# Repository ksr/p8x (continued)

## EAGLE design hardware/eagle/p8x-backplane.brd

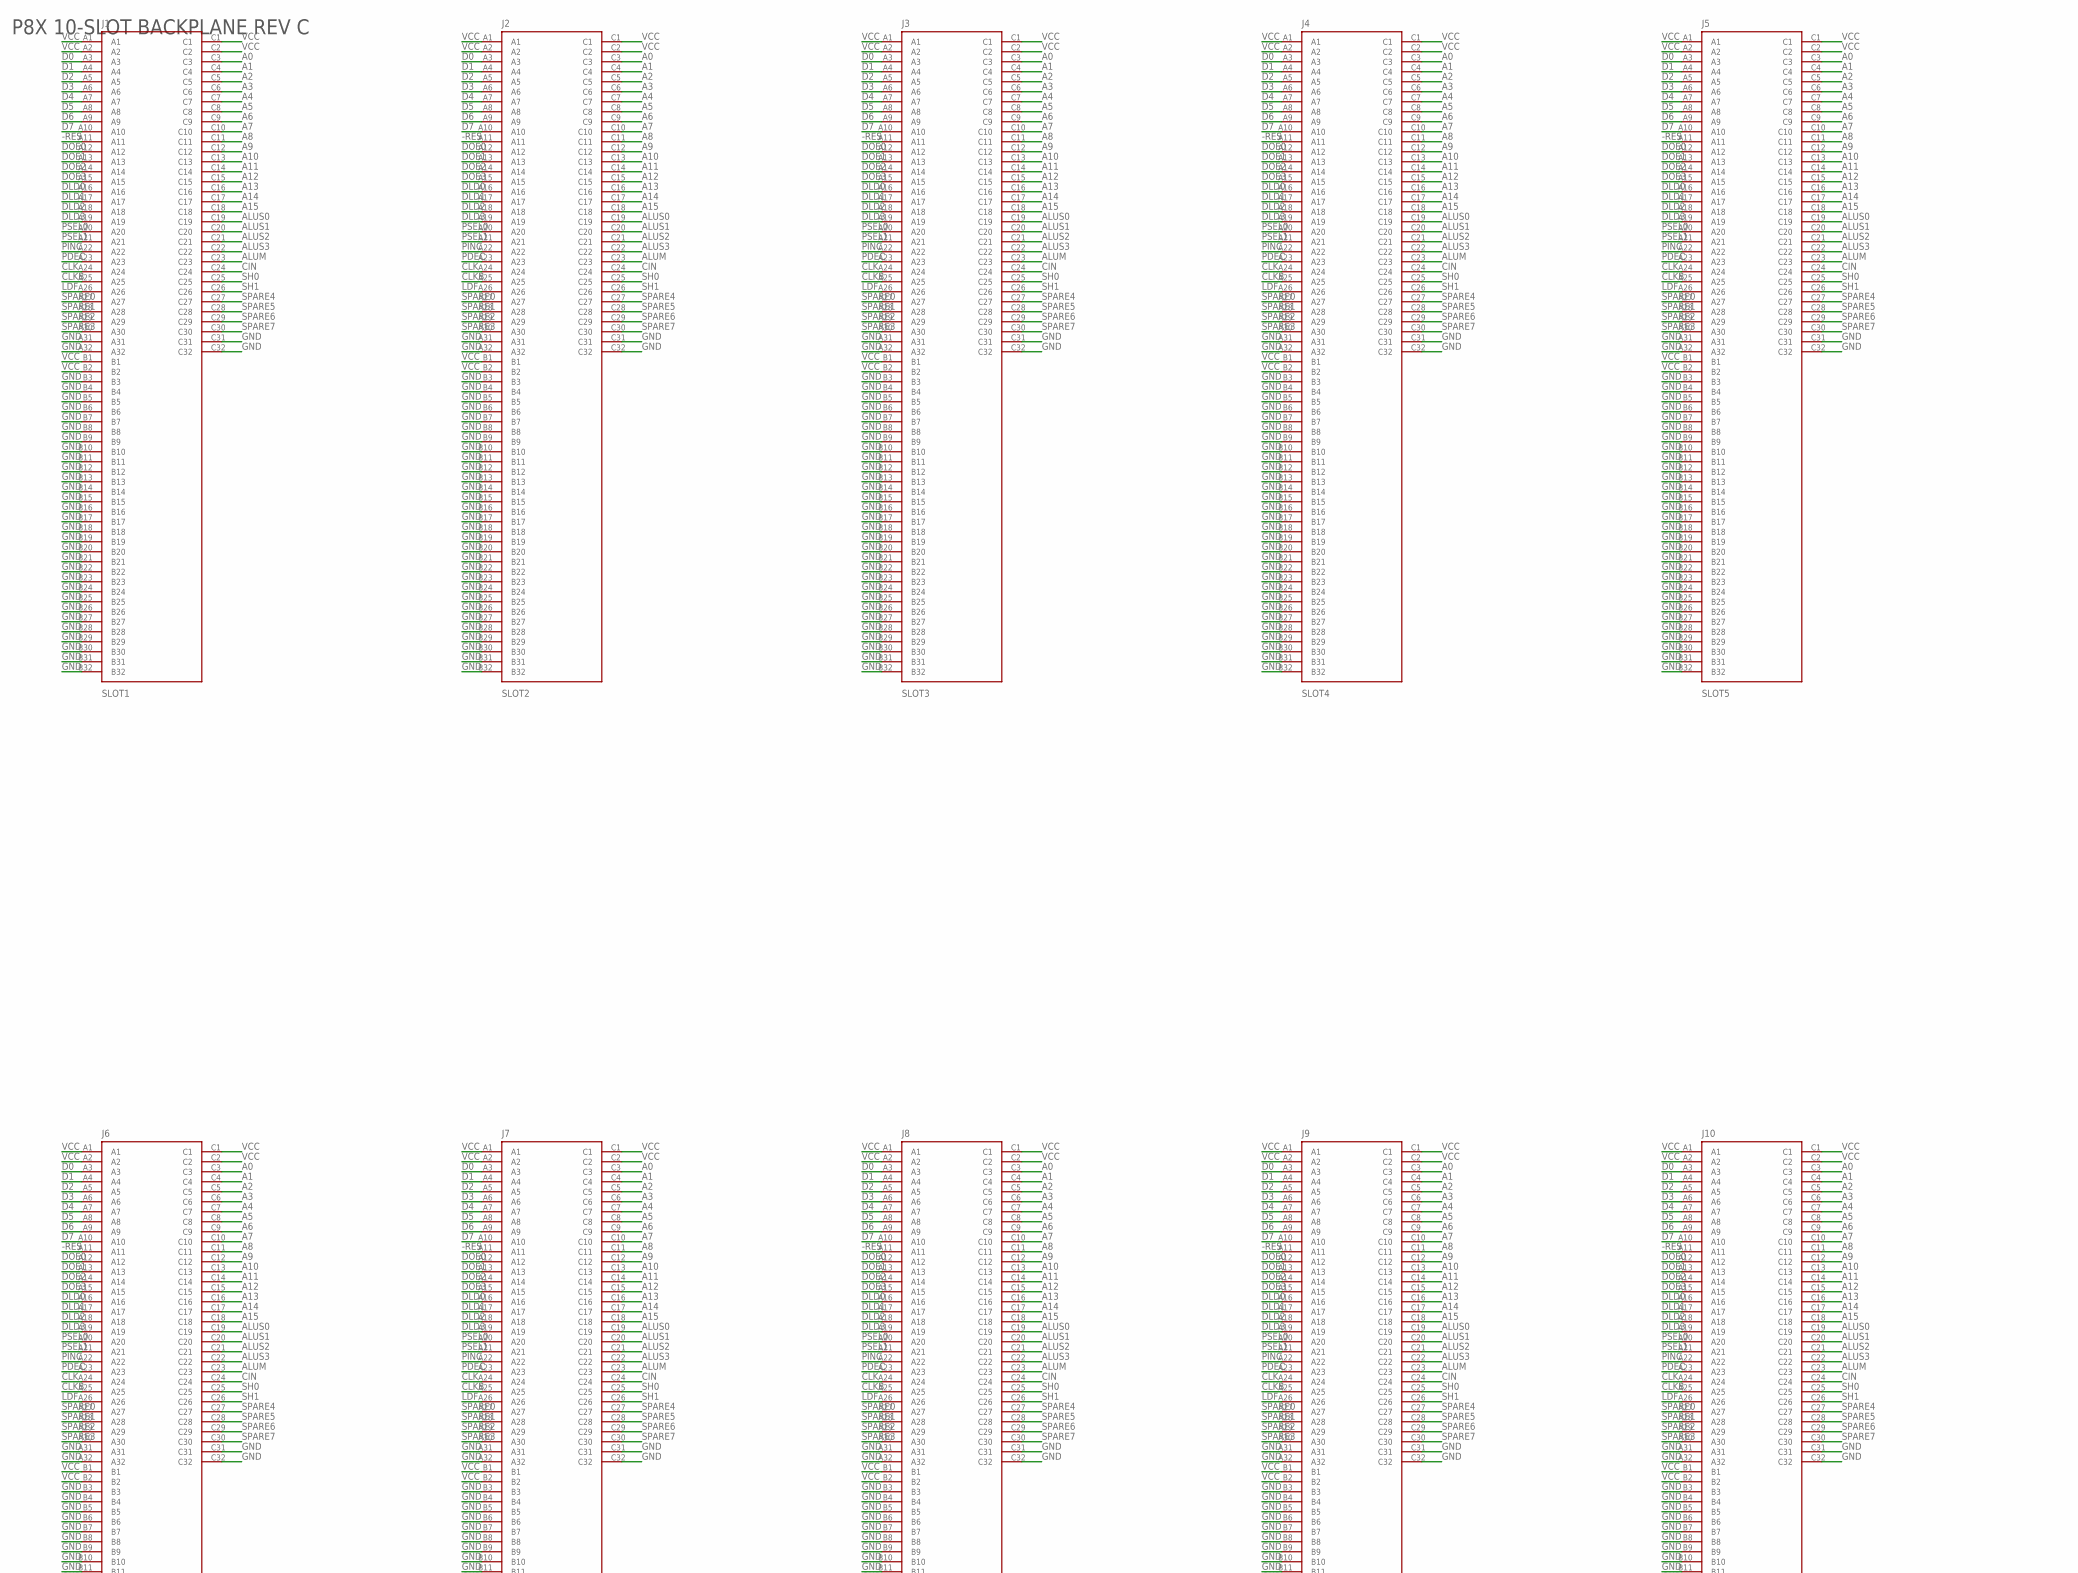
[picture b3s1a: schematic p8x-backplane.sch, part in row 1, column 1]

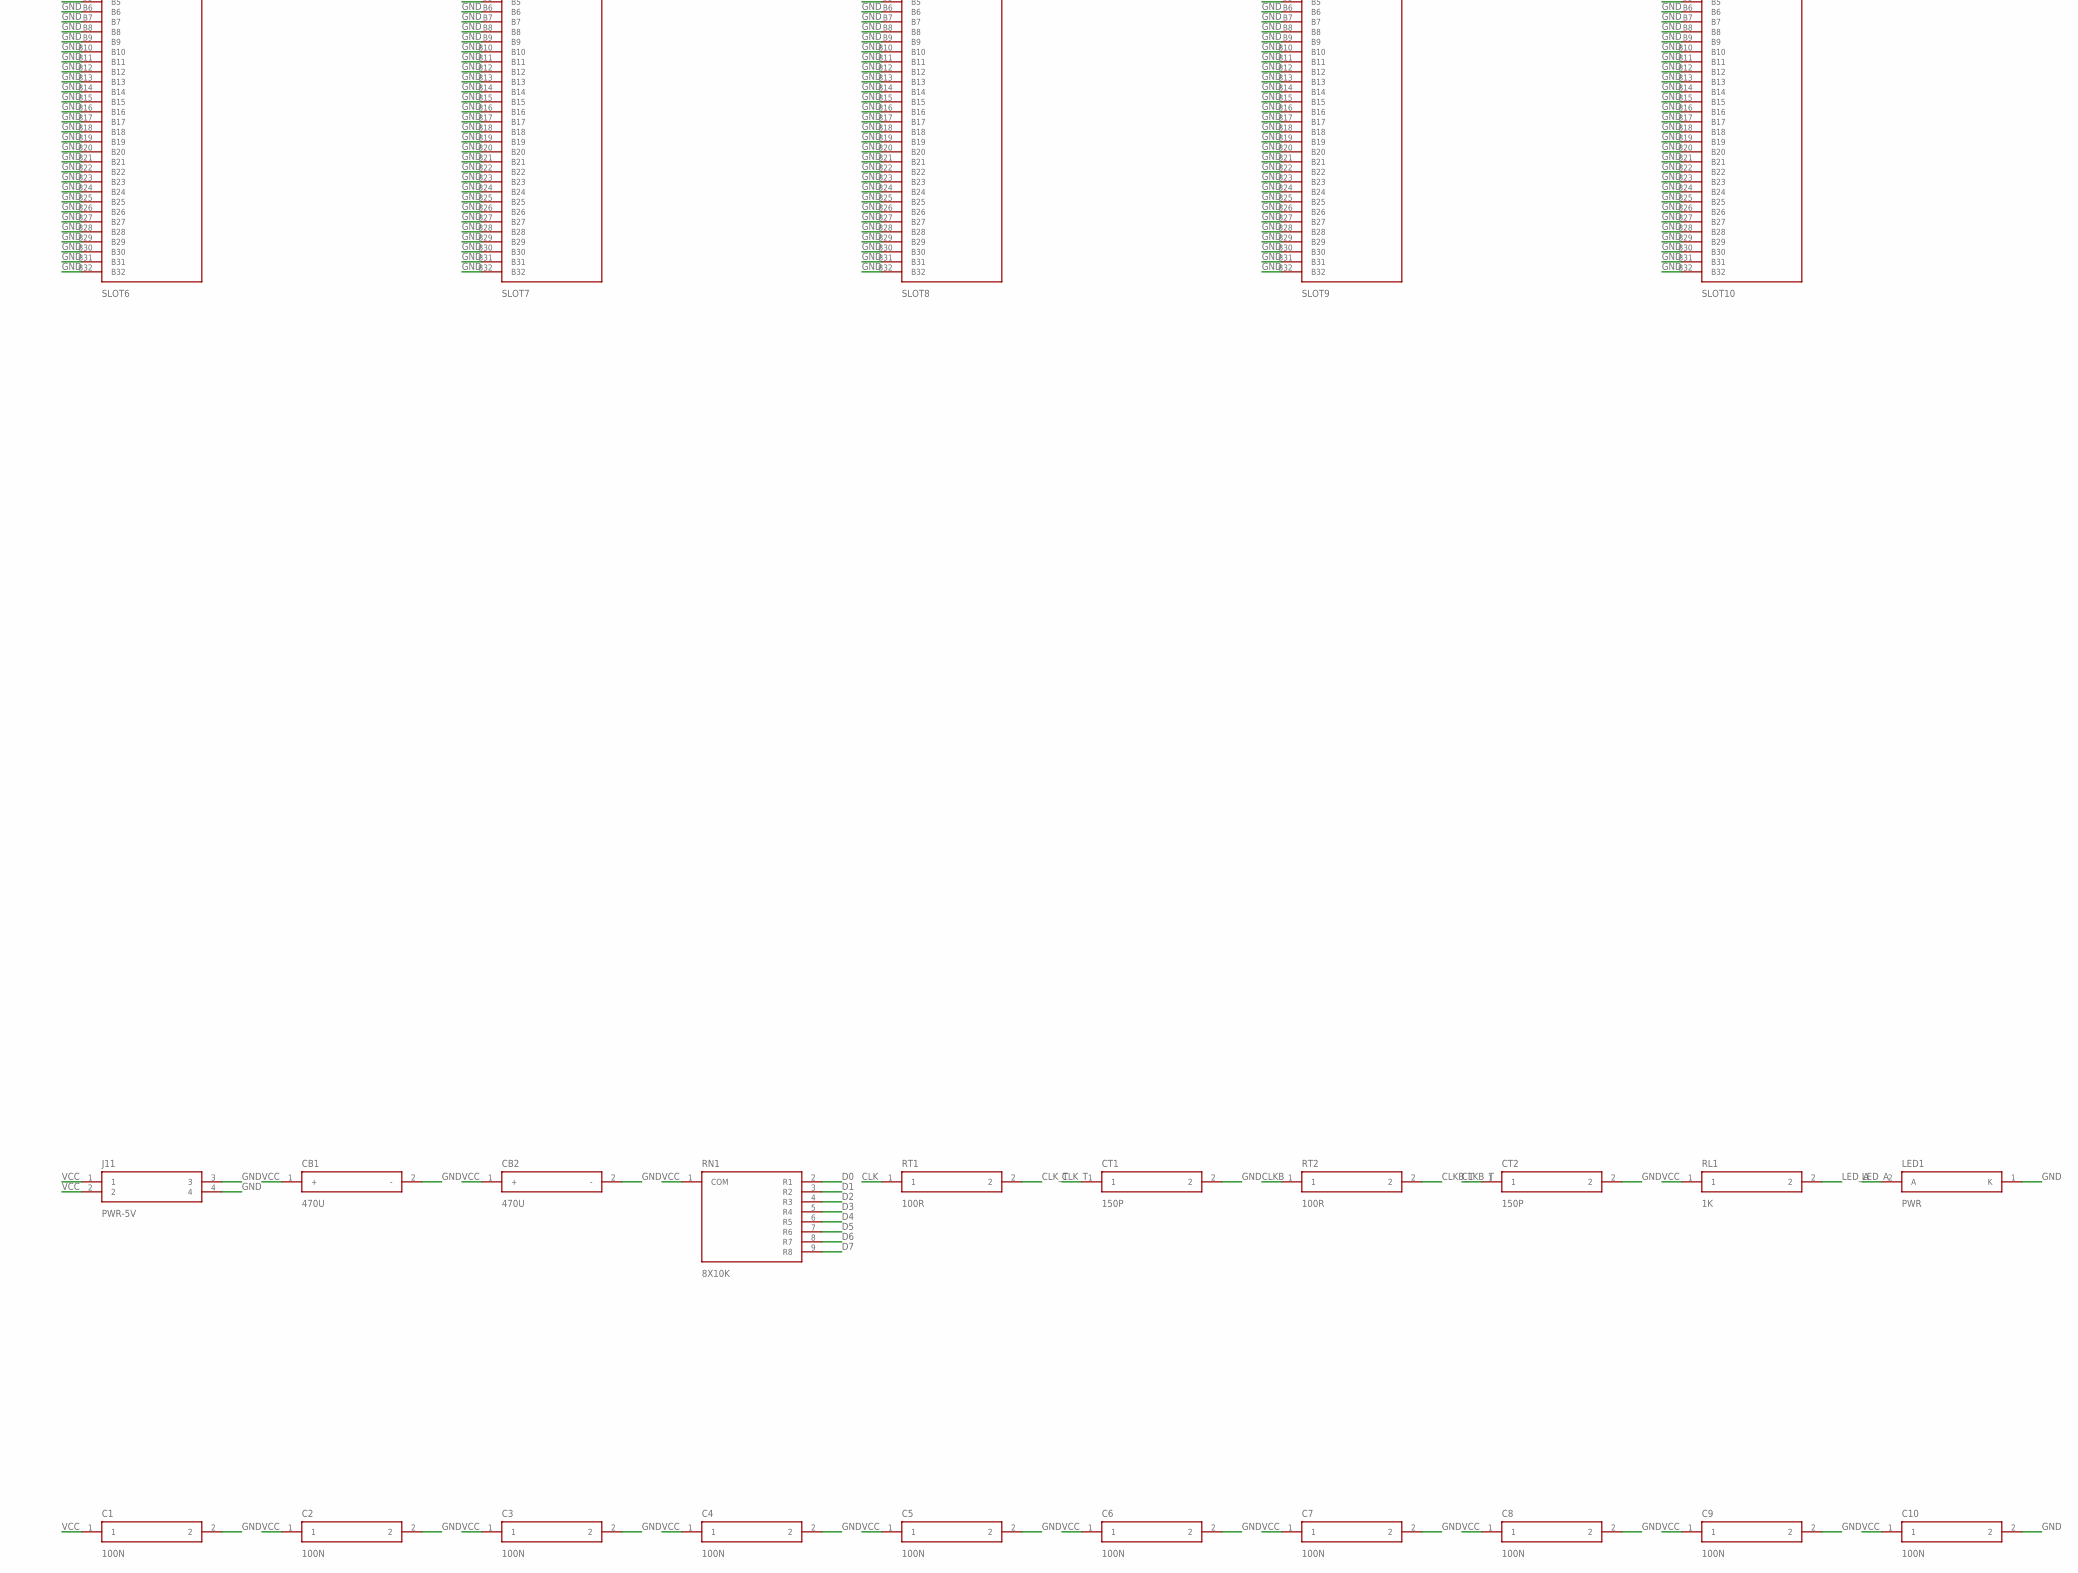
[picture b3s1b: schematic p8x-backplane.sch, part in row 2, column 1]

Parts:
C1, C2, C3, C4, C5, C6, C7, C8, C9, C10: 100N; C_DISC
CB1, CB2: 470U; CP_RADIAL
CT1, CT2: 150P; C_DISC
J1: SLOT1; DIN96
J2: SLOT2; DIN96
J3: SLOT3; DIN96
J4: SLOT4; DIN96
J5: SLOT5; DIN96
J6: SLOT6; DIN96
J7: SLOT7; DIN96
J8: SLOT8; DIN96
J9: SLOT9; DIN96
J10: SLOT10; DIN96
J11: PWR-5V; TB4
LED1: PWR; LED5
RL1: 1K; R_AXIAL
RN1: 8X10K; SIP9
RT1, RT2: 100R; R_AXIAL

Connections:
-RES: J1.A11, J2.A11, J3.A11, J4.A11, J5.A11, J6.A11, J7.A11, J8.A11, J9.A11, J10.A11
A0: J1.C3, J2.C3, J3.C3, J4.C3, J5.C3, J6.C3, J7.C3, J8.C3, J9.C3, J10.C3
A1: J1.C4, J2.C4, J3.C4, J4.C4, J5.C4, J6.C4, J7.C4, J8.C4, J9.C4, J10.C4
A2: J1.C5, J2.C5, J3.C5, J4.C5, J5.C5, J6.C5, J7.C5, J8.C5, J9.C5, J10.C5
A3: J1.C6, J2.C6, J3.C6, J4.C6, J5.C6, J6.C6, J7.C6, J8.C6, J9.C6, J10.C6
A4: J1.C7, J2.C7, J3.C7, J4.C7, J5.C7, J6.C7, J7.C7, J8.C7, J9.C7, J10.C7
A5: J1.C8, J2.C8, J3.C8, J4.C8, J5.C8, J6.C8, J7.C8, J8.C8, J9.C8, J10.C8
A6: J1.C9, J2.C9, J3.C9, J4.C9, J5.C9, J6.C9, J7.C9, J8.C9, J9.C9, J10.C9
A7: J1.C10, J2.C10, J3.C10, J4.C10, J5.C10, J6.C10, J7.C10, J8.C10, J9.C10, J10.C10
A8: J1.C11, J2.C11, J3.C11, J4.C11, J5.C11, J6.C11, J7.C11, J8.C11, J9.C11, J10.C11
A9: J1.C12, J2.C12, J3.C12, J4.C12, J5.C12, J6.C12, J7.C12, J8.C12, J9.C12, J10.C12
A10: J1.C13, J2.C13, J3.C13, J4.C13, J5.C13, J6.C13, J7.C13, J8.C13, J9.C13, J10.C13
A11: J1.C14, J2.C14, J3.C14, J4.C14, J5.C14, J6.C14, J7.C14, J8.C14, J9.C14, J10.C14
A12: J1.C15, J2.C15, J3.C15, J4.C15, J5.C15, J6.C15, J7.C15, J8.C15, J9.C15, J10.C15
A13: J1.C16, J2.C16, J3.C16, J4.C16, J5.C16, J6.C16, J7.C16, J8.C16, J9.C16, J10.C16
A14: J1.C17, J2.C17, J3.C17, J4.C17, J5.C17, J6.C17, J7.C17, J8.C17, J9.C17, J10.C17
A15: J1.C18, J2.C18, J3.C18, J4.C18, J5.C18, J6.C18, J7.C18, J8.C18, J9.C18, J10.C18
ALUM: J1.C23, J2.C23, J3.C23, J4.C23, J5.C23, J6.C23, J7.C23, J8.C23, J9.C23, J10.C23
ALUS0: J1.C19, J2.C19, J3.C19, J4.C19, J5.C19, J6.C19, J7.C19, J8.C19, J9.C19, J10.C19
ALUS1: J1.C20, J2.C20, J3.C20, J4.C20, J5.C20, J6.C20, J7.C20, J8.C20, J9.C20, J10.C20
ALUS2: J1.C21, J2.C21, J3.C21, J4.C21, J5.C21, J6.C21, J7.C21, J8.C21, J9.C21, J10.C21
ALUS3: J1.C22, J2.C22, J3.C22, J4.C22, J5.C22, J6.C22, J7.C22, J8.C22, J9.C22, J10.C22
CIN: J1.C24, J2.C24, J3.C24, J4.C24, J5.C24, J6.C24, J7.C24, J8.C24, J9.C24, J10.C24
CLK: J1.A24, J2.A24, J3.A24, J4.A24, J5.A24, J6.A24, J7.A24, J8.A24, J9.A24, J10.A24, RT1.1
CLKB: J1.A25, J2.A25, J3.A25, J4.A25, J5.A25, J6.A25, J7.A25, J8.A25, J9.A25, J10.A25, RT2.1
CLKB_T: CT2.1, RT2.2
CLK_T: CT1.1, RT1.2
D0: J1.A3, J2.A3, J3.A3, J4.A3, J5.A3, J6.A3, J7.A3, J8.A3, J9.A3, J10.A3, RN1.2 (R1)
D1: J1.A4, J2.A4, J3.A4, J4.A4, J5.A4, J6.A4, J7.A4, J8.A4, J9.A4, J10.A4, RN1.3 (R2)
D2: J1.A5, J2.A5, J3.A5, J4.A5, J5.A5, J6.A5, J7.A5, J8.A5, J9.A5, J10.A5, RN1.4 (R3)
D3: J1.A6, J2.A6, J3.A6, J4.A6, J5.A6, J6.A6, J7.A6, J8.A6, J9.A6, J10.A6, RN1.5 (R4)
D4: J1.A7, J2.A7, J3.A7, J4.A7, J5.A7, J6.A7, J7.A7, J8.A7, J9.A7, J10.A7, RN1.6 (R5)
D5: J1.A8, J2.A8, J3.A8, J4.A8, J5.A8, J6.A8, J7.A8, J8.A8, J9.A8, J10.A8, RN1.7 (R6)
D6: J1.A9, J2.A9, J3.A9, J4.A9, J5.A9, J6.A9, J7.A9, J8.A9, J9.A9, J10.A9, RN1.8 (R7)
D7: J1.A10, J2.A10, J3.A10, J4.A10, J5.A10, J6.A10, J7.A10, J8.A10, J9.A10, J10.A10, RN1.9 (R8)
DLD0: J1.A16, J2.A16, J3.A16, J4.A16, J5.A16, J6.A16, J7.A16, J8.A16, J9.A16, J10.A16
DLD1: J1.A17, J2.A17, J3.A17, J4.A17, J5.A17, J6.A17, J7.A17, J8.A17, J9.A17, J10.A17
DLD2: J1.A18, J2.A18, J3.A18, J4.A18, J5.A18, J6.A18, J7.A18, J8.A18, J9.A18, J10.A18
DLD3: J1.A19, J2.A19, J3.A19, J4.A19, J5.A19, J6.A19, J7.A19, J8.A19, J9.A19, J10.A19
DOE0: J1.A12, J2.A12, J3.A12, J4.A12, J5.A12, J6.A12, J7.A12, J8.A12, J9.A12, J10.A12
DOE1: J1.A13, J2.A13, J3.A13, J4.A13, J5.A13, J6.A13, J7.A13, J8.A13, J9.A13, J10.A13
DOE2: J1.A14, J2.A14, J3.A14, J4.A14, J5.A14, J6.A14, J7.A14, J8.A14, J9.A14, J10.A14
DOE3: J1.A15, J2.A15, J3.A15, J4.A15, J5.A15, J6.A15, J7.A15, J8.A15, J9.A15, J10.A15
GND: C1.2, C2.2, C3.2, C4.2, C5.2, C6.2, C7.2, C8.2, C9.2, C10.2, CB1.2 (-), CB2.2 (-), CT1.2, CT2.2, J1.A31, J1.A32, J1.B3, J1.B4, J1.B5, J1.B6, J1.B7, J1.B8, J1.B9, J1.B10, J1.B11, J1.B12, J1.B13, J1.B14, J1.B15, J1.B16, J1.B17, J1.B18, J1.B19, J1.B20, J1.B21, J1.B22, J1.B23, J1.B24, J1.B25, J1.B26, J1.B27, J1.B28, J1.B29, J1.B30, J1.B31, J1.B32, J1.C31, J1.C32, J2.A31, J2.A32, J2.B3, J2.B4, J2.B5, J2.B6, J2.B7, J2.B8, J2.B9, J2.B10, J2.B11, J2.B12, J2.B13, J2.B14, J2.B15, J2.B16, J2.B17, J2.B18, J2.B19, J2.B20, J2.B21, J2.B22, J2.B23, J2.B24, J2.B25, J2.B26, J2.B27, J2.B28, J2.B29, J2.B30, J2.B31, J2.B32, J2.C31, J2.C32, J3.A31, J3.A32, J3.B3, J3.B4, J3.B5, J3.B6, J3.B7, J3.B8, J3.B9, J3.B10, J3.B11, J3.B12, J3.B13, J3.B14, J3.B15, J3.B16, J3.B17, J3.B18, J3.B19, J3.B20, J3.B21, J3.B22, J3.B23, J3.B24, J3.B25, J3.B26, J3.B27, J3.B28, J3.B29, J3.B30, J3.B31, J3.B32, J3.C31, J3.C32, J4.A31, J4.A32, J4.B3, J4.B4, J4.B5, J4.B6, J4.B7, J4.B8, J4.B9, J4.B10, J4.B11, J4.B12, J4.B13, J4.B14, J4.B15, J4.B16, J4.B17, J4.B18, J4.B19, J4.B20, J4.B21, J4.B22, J4.B23, J4.B24, J4.B25, J4.B26, J4.B27, J4.B28, J4.B29, J4.B30, J4.B31, J4.B32, J4.C31, J4.C32, J5.A31, J5.A32, J5.B3, J5.B4, J5.B5, J5.B6, J5.B7, J5.B8, J5.B9, J5.B10, J5.B11, J5.B12, J5.B13, J5.B14, J5.B15, J5.B16, J5.B17, J5.B18, J5.B19, J5.B20, J5.B21, J5.B22, J5.B23, J5.B24, J5.B25, J5.B26, J5.B27, J5.B28, J5.B29, J5.B30, J5.B31, J5.B32, J5.C31, J5.C32, J6.A31, J6.A32, J6.B3, J6.B4, J6.B5, J6.B6, J6.B7, J6.B8, J6.B9, J6.B10, J6.B11, J6.B12, J6.B13, J6.B14, J6.B15, J6.B16, J6.B17, J6.B18, J6.B19, J6.B20, J6.B21, J6.B22, J6.B23, J6.B24, J6.B25, J6.B26, J6.B27, J6.B28, J6.B29, J6.B30, J6.B31, J6.B32, J6.C31, J6.C32, J7.A31, J7.A32, J7.B3, J7.B4, J7.B5, J7.B6, J7.B7, J7.B8, J7.B9, J7.B10, J7.B11, J7.B12, J7.B13, J7.B14, J7.B15, J7.B16, J7.B17, J7.B18, J7.B19, J7.B20, J7.B21, J7.B22, J7.B23, J7.B24, J7.B25, J7.B26, J7.B27, J7.B28, J7.B29, J7.B30, J7.B31, J7.B32, J7.C31, J7.C32, J8.A31, J8.A32, J8.B3, J8.B4, J8.B5, J8.B6, J8.B7, J8.B8, J8.B9, J8.B10, J8.B11, J8.B12, J8.B13, J8.B14, J8.B15, J8.B16, J8.B17, J8.B18, J8.B19, J8.B20, J8.B21, J8.B22, J8.B23, J8.B24, J8.B25, J8.B26, J8.B27, J8.B28, J8.B29, J8.B30, J8.B31, J8.B32, J8.C31, J8.C32, J9.A31, J9.A32, J9.B3, J9.B4, J9.B5, J9.B6, J9.B7, J9.B8, J9.B9, J9.B10, J9.B11, J9.B12, J9.B13, J9.B14, J9.B15, J9.B16, J9.B17, J9.B18, J9.B19, J9.B20, J9.B21, J9.B22, J9.B23, J9.B24, J9.B25, J9.B26, J9.B27, J9.B28, J9.B29, J9.B30, J9.B31, J9.B32, J9.C31, J9.C32, J10.A31, J10.A32, J10.B3, J10.B4, J10.B5, J10.B6, J10.B7, J10.B8, J10.B9, J10.B10, J10.B11, J10.B12, J10.B13, J10.B14, J10.B15, J10.B16, J10.B17, J10.B18, J10.B19, J10.B20, J10.B21, J10.B22, J10.B23, J10.B24, J10.B25, J10.B26, J10.B27, J10.B28, J10.B29, J10.B30, J10.B31, J10.B32, J10.C31, J10.C32, J11.3, J11.4, LED1.1 (K)
LDF: J1.A26, J2.A26, J3.A26, J4.A26, J5.A26, J6.A26, J7.A26, J8.A26, J9.A26, J10.A26
LED_A: LED1.2 (A), RL1.2
PDEC: J1.A23, J2.A23, J3.A23, J4.A23, J5.A23, J6.A23, J7.A23, J8.A23, J9.A23, J10.A23
PINC: J1.A22, J2.A22, J3.A22, J4.A22, J5.A22, J6.A22, J7.A22, J8.A22, J9.A22, J10.A22
PSEL0: J1.A20, J2.A20, J3.A20, J4.A20, J5.A20, J6.A20, J7.A20, J8.A20, J9.A20, J10.A20
PSEL1: J1.A21, J2.A21, J3.A21, J4.A21, J5.A21, J6.A21, J7.A21, J8.A21, J9.A21, J10.A21
SH0: J1.C25, J2.C25, J3.C25, J4.C25, J5.C25, J6.C25, J7.C25, J8.C25, J9.C25, J10.C25
SH1: J1.C26, J2.C26, J3.C26, J4.C26, J5.C26, J6.C26, J7.C26, J8.C26, J9.C26, J10.C26
SPARE0: J1.A27, J2.A27, J3.A27, J4.A27, J5.A27, J6.A27, J7.A27, J8.A27, J9.A27, J10.A27
SPARE1: J1.A28, J2.A28, J3.A28, J4.A28, J5.A28, J6.A28, J7.A28, J8.A28, J9.A28, J10.A28
SPARE2: J1.A29, J2.A29, J3.A29, J4.A29, J5.A29, J6.A29, J7.A29, J8.A29, J9.A29, J10.A29
SPARE3: J1.A30, J2.A30, J3.A30, J4.A30, J5.A30, J6.A30, J7.A30, J8.A30, J9.A30, J10.A30
SPARE4: J1.C27, J2.C27, J3.C27, J4.C27, J5.C27, J6.C27, J7.C27, J8.C27, J9.C27, J10.C27
SPARE5: J1.C28, J2.C28, J3.C28, J4.C28, J5.C28, J6.C28, J7.C28, J8.C28, J9.C28, J10.C28
SPARE6: J1.C29, J2.C29, J3.C29, J4.C29, J5.C29, J6.C29, J7.C29, J8.C29, J9.C29, J10.C29
SPARE7: J1.C30, J2.C30, J3.C30, J4.C30, J5.C30, J6.C30, J7.C30, J8.C30, J9.C30, J10.C30
VCC: C1.1, C2.1, C3.1, C4.1, C5.1, C6.1, C7.1, C8.1, C9.1, C10.1, CB1.1 (+), CB2.1 (+), J1.A1, J1.A2, J1.B1, J1.B2, J1.C1, J1.C2, J2.A1, J2.A2, J2.B1, J2.B2, J2.C1, J2.C2, J3.A1, J3.A2, J3.B1, J3.B2, J3.C1, J3.C2, J4.A1, J4.A2, J4.B1, J4.B2, J4.C1, J4.C2, J5.A1, J5.A2, J5.B1, J5.B2, J5.C1, J5.C2, J6.A1, J6.A2, J6.B1, J6.B2, J6.C1, J6.C2, J7.A1, J7.A2, J7.B1, J7.B2, J7.C1, J7.C2, J8.A1, J8.A2, J8.B1, J8.B2, J8.C1, J8.C2, J9.A1, J9.A2, J9.B1, J9.B2, J9.C1, J9.C2, J10.A1, J10.A2, J10.B1, J10.B2, J10.C1, J10.C2, J11.1, J11.2, RL1.1, RN1.1 (COM)

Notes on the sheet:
P8X 10-SLOT BACKPLANE REV C

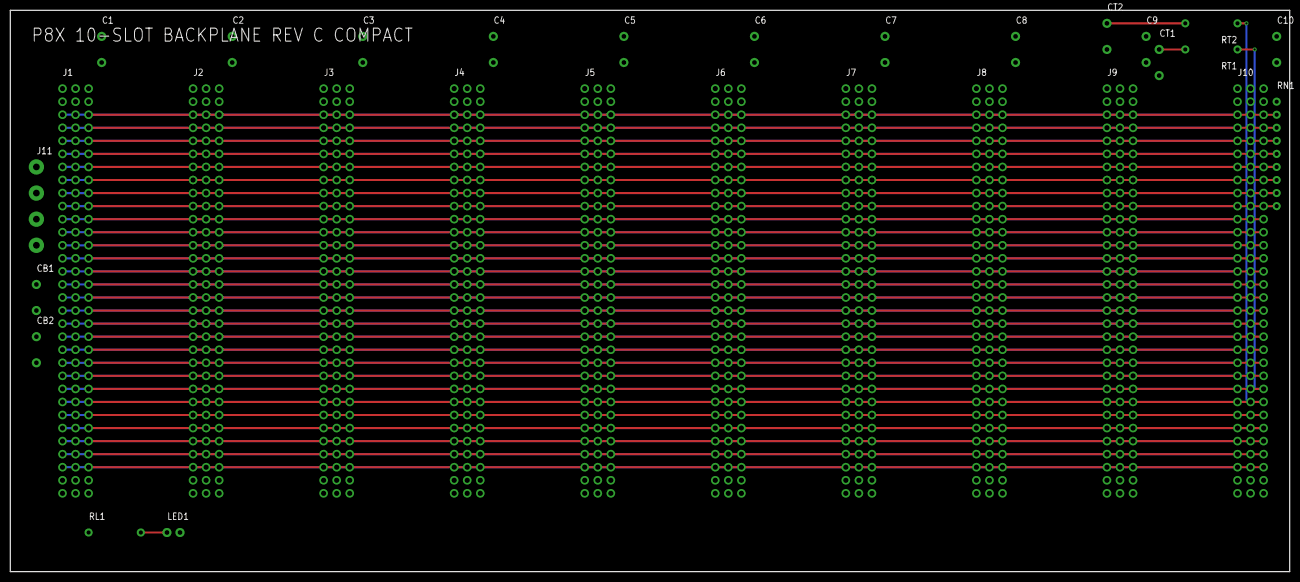
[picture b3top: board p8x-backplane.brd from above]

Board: 4 copper layers, 248.9 x 109.2 mm, 30 parts (0 on the bottom side), 61 nets.

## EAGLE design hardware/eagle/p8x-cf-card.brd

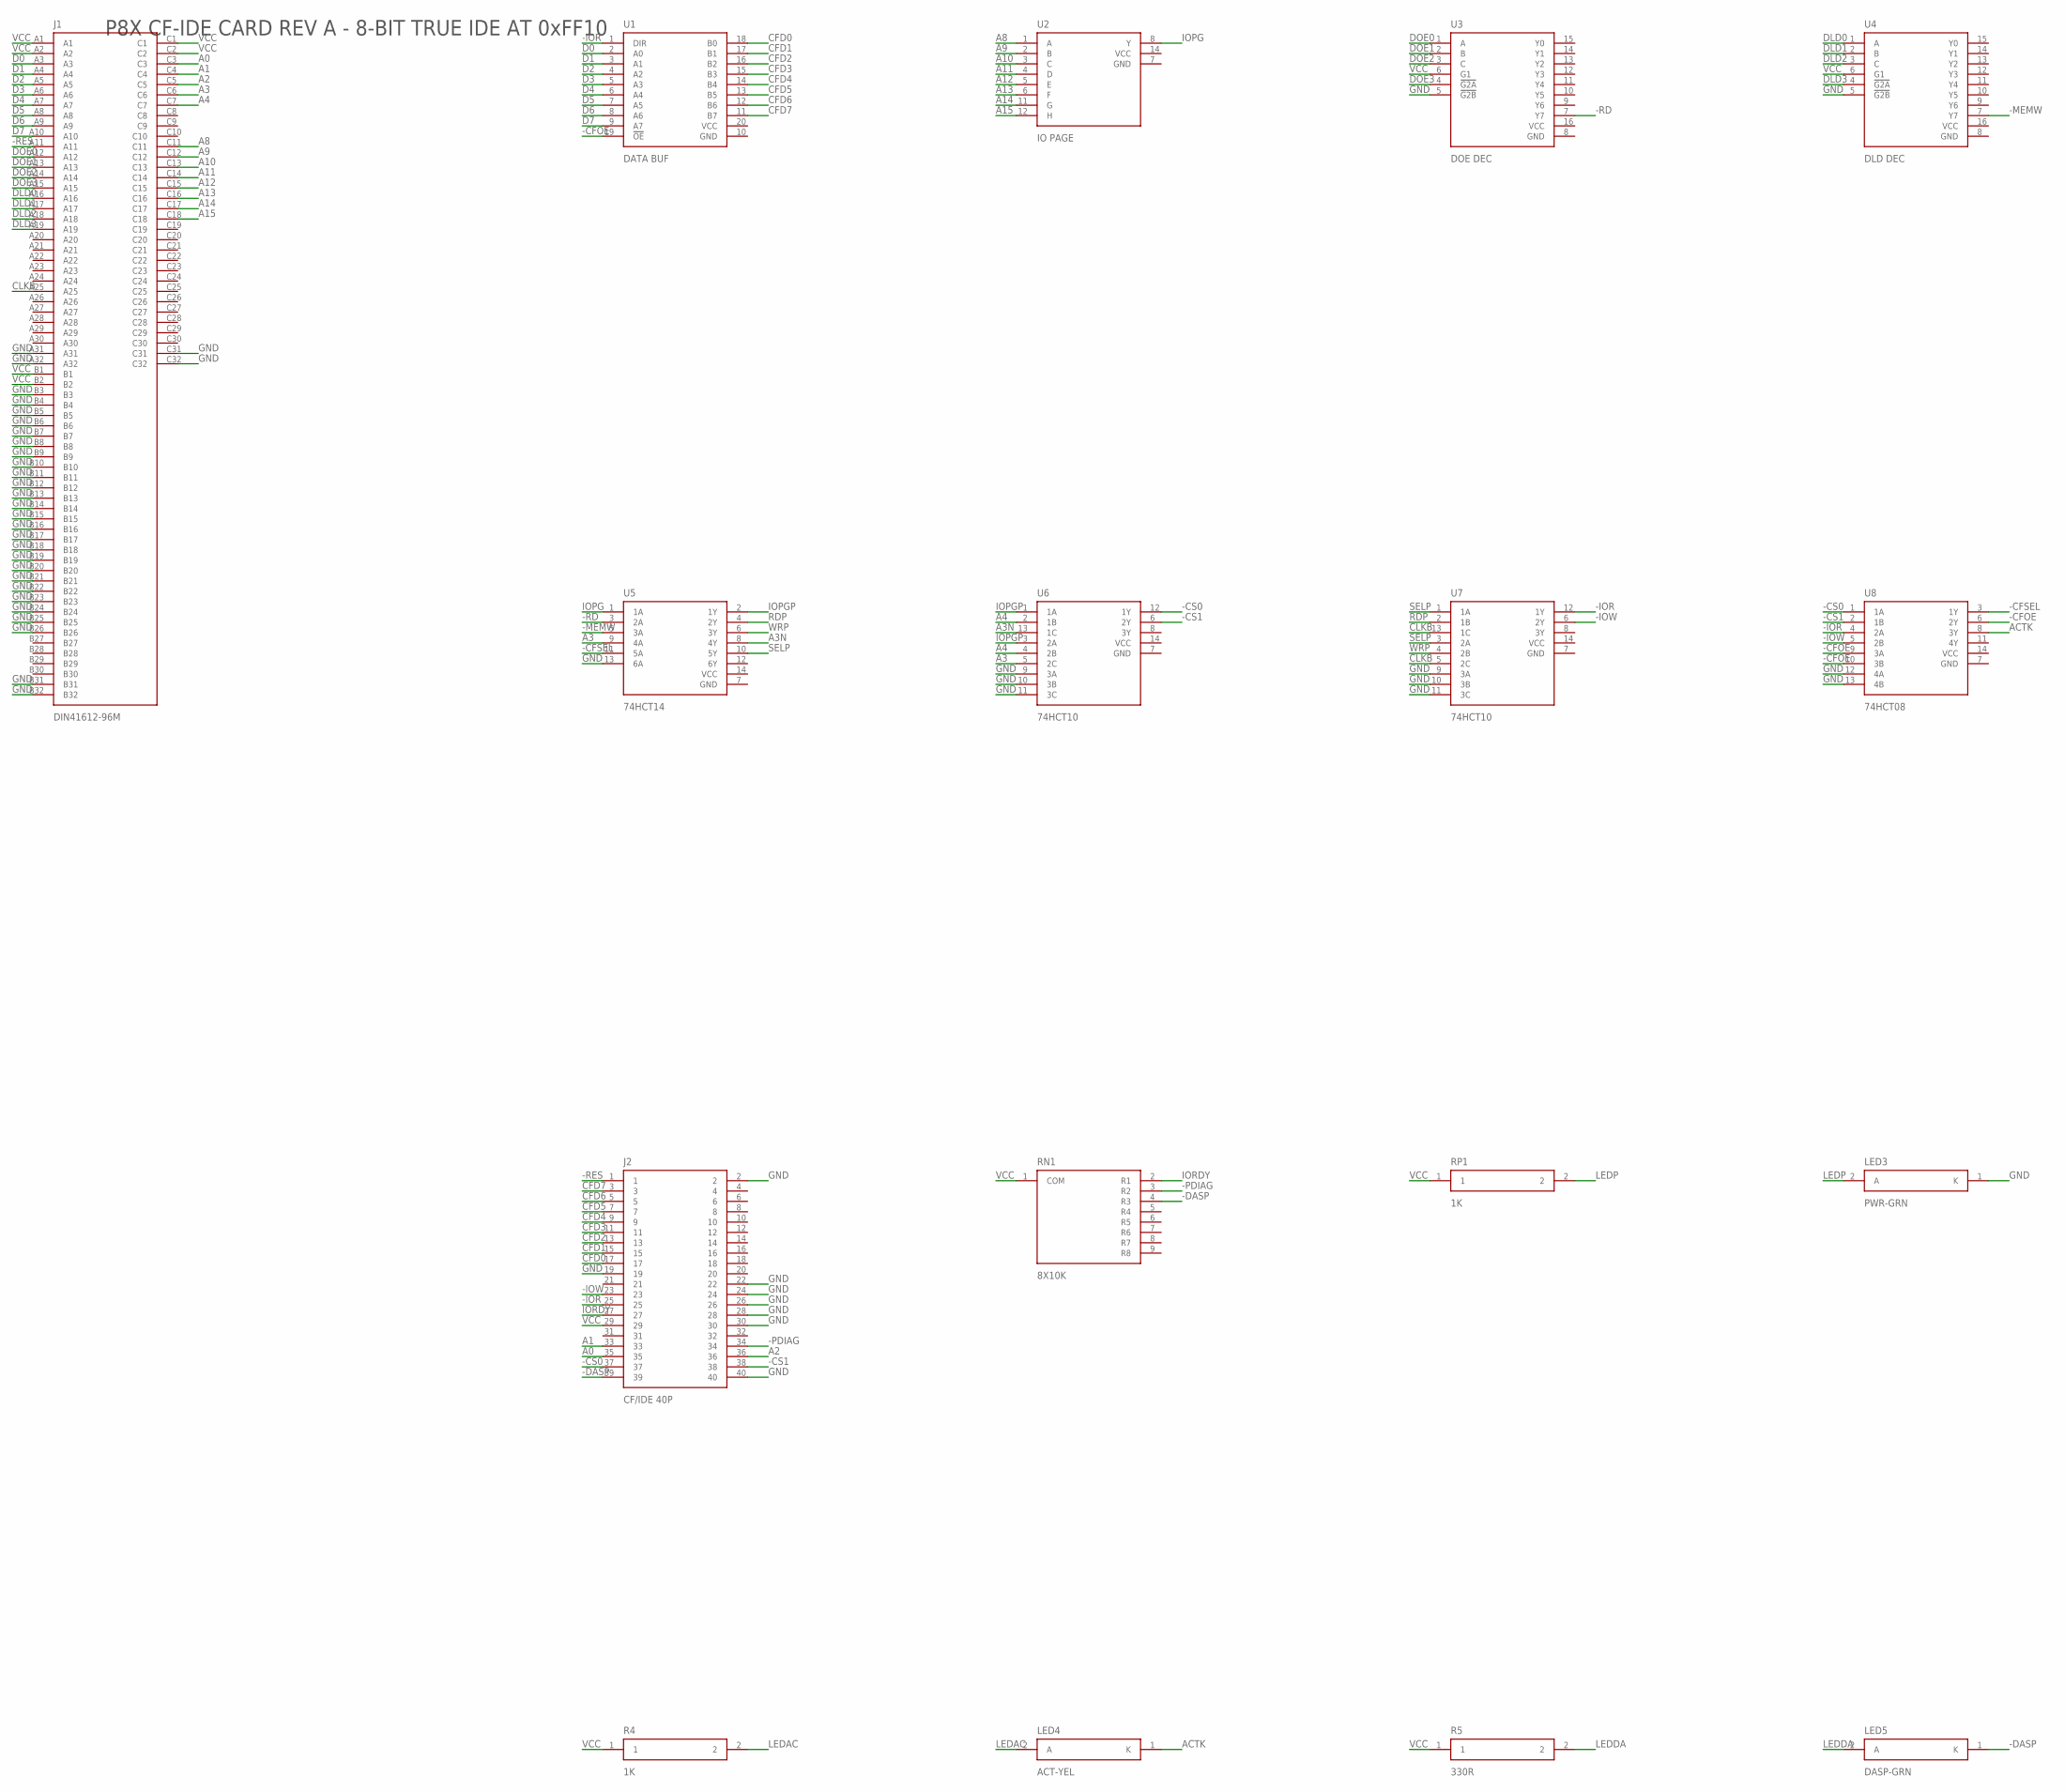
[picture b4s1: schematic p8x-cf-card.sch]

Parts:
J1: DIN41612-96M; DIN96
J2: CF/IDE 40P; HDR40
LED3: PWR-GRN; LED5
LED4: ACT-YEL; LED5
LED5: DASP-GRN; LED5
R4: 1K; R_AXIAL
R5: 330R; R_AXIAL
RN1: 8X10K; SIP9
RP1: 1K; R_AXIAL
U1: DATA BUF; DIP20
U2: IO PAGE; DIP14
U3: DOE DEC; DIP16
U4: DLD DEC; DIP16
U5: 74HCT14; DIP14
U6, U7: 74HCT10; DIP14
U8: 74HCT08; DIP14

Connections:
-CFOE: U1.19 (!OE), U8.6 (2Y), U8.9 (3A), U8.10 (3B)
-CFSEL: U5.11 (5A), U8.3 (1Y)
-CS0: J2.37, U6.12 (1Y), U8.1 (1A)
-CS1: J2.38, U6.6 (2Y), U8.2 (1B)
-DASP: J2.39, LED5.1 (K), RN1.4 (R3)
-IOR: J2.25, U1.1 (DIR), U7.12 (1Y), U8.4 (2A)
-IOW: J2.23, U7.6 (2Y), U8.5 (2B)
-MEMW: U4.7 (Y7), U5.5 (3A)
-PDIAG: J2.34, RN1.3 (R2)
-RD: U3.7 (Y7), U5.3 (2A)
-RES: J1.A11, J2.1
A0: J1.C3, J2.35
A1: J1.C4, J2.33
A2: J1.C5, J2.36
A3: J1.C6, U5.9 (4A), U6.5 (2C)
A3N: U5.8 (4Y), U6.13 (1C)
A4: J1.C7, U6.2 (1B), U6.4 (2B)
A8: J1.C11, U2.1 (A)
A9: J1.C12, U2.2 (B)
A10: J1.C13, U2.3 (C)
A11: J1.C14, U2.4 (D)
A12: J1.C15, U2.5 (E)
A13: J1.C16, U2.6 (F)
A14: J1.C17, U2.11 (G)
A15: J1.C18, U2.12 (H)
ACTK: LED4.1 (K), U8.8 (3Y)
CFD0: J2.17, U1.18 (B0)
CFD1: J2.15, U1.17 (B1)
CFD2: J2.13, U1.16 (B2)
CFD3: J2.11, U1.15 (B3)
CFD4: J2.9, U1.14 (B4)
CFD5: J2.7, U1.13 (B5)
CFD6: J2.5, U1.12 (B6)
CFD7: J2.3, U1.11 (B7)
CLKB: J1.A25, U7.5 (2C), U7.13 (1C)
D0: J1.A3, U1.2 (A0)
D1: J1.A4, U1.3 (A1)
D2: J1.A5, U1.4 (A2)
D3: J1.A6, U1.5 (A3)
D4: J1.A7, U1.6 (A4)
D5: J1.A8, U1.7 (A5)
D6: J1.A9, U1.8 (A6)
D7: J1.A10, U1.9 (A7)
DLD0: J1.A16, U4.1 (A)
DLD1: J1.A17, U4.2 (B)
DLD2: J1.A18, U4.3 (C)
DLD3: J1.A19, U4.4 (!G2A)
DOE0: J1.A12, U3.1 (A)
DOE1: J1.A13, U3.2 (B)
DOE2: J1.A14, U3.3 (C)
DOE3: J1.A15, U3.4 (!G2A)
GND: J1.A31, J1.A32, J1.B3, J1.B4, J1.B5, J1.B6, J1.B7, J1.B8, J1.B9, J1.B10, J1.B11, J1.B12, J1.B13, J1.B14, J1.B15, J1.B16, J1.B17, J1.B18, J1.B19, J1.B20, J1.B21, J1.B22, J1.B23, J1.B24, J1.B25, J1.B26, J1.B31, J1.B32, J1.C31, J1.C32, J2.2, J2.19, J2.22, J2.24, J2.26, J2.28, J2.30, J2.40, LED3.1 (K), U3.5 (!G2B), U4.5 (!G2B), U5.13 (6A), U6.9 (3A), U6.10 (3B), U6.11 (3C), U7.9 (3A), U7.10 (3B), U7.11 (3C), U8.12 (4A), U8.13 (4B)
IOPG: U2.8 (Y), U5.1 (1A)
IOPGP: U5.2 (1Y), U6.1 (1A), U6.3 (2A)
IORDY: J2.27, RN1.2 (R1)
LEDAC: LED4.2 (A), R4.2
LEDDA: LED5.2 (A), R5.2
LEDP: LED3.2 (A), RP1.2
RDP: U5.4 (2Y), U7.2 (1B)
SELP: U5.10 (5Y), U7.1 (1A), U7.3 (2A)
VCC: J1.A1, J1.A2, J1.B1, J1.B2, J1.C1, J1.C2, J2.29, R4.1, R5.1, RN1.1 (COM), RP1.1, U3.6 (G1), U4.6 (G1)
WRP: U5.6 (3Y), U7.4 (2B)

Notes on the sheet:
P8X CF-IDE CARD REV A - 8-BIT TRUE IDE AT 0xFF10

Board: 4 copper layers, 17 parts (0 on the bottom side), 62 nets, no tracks yet.

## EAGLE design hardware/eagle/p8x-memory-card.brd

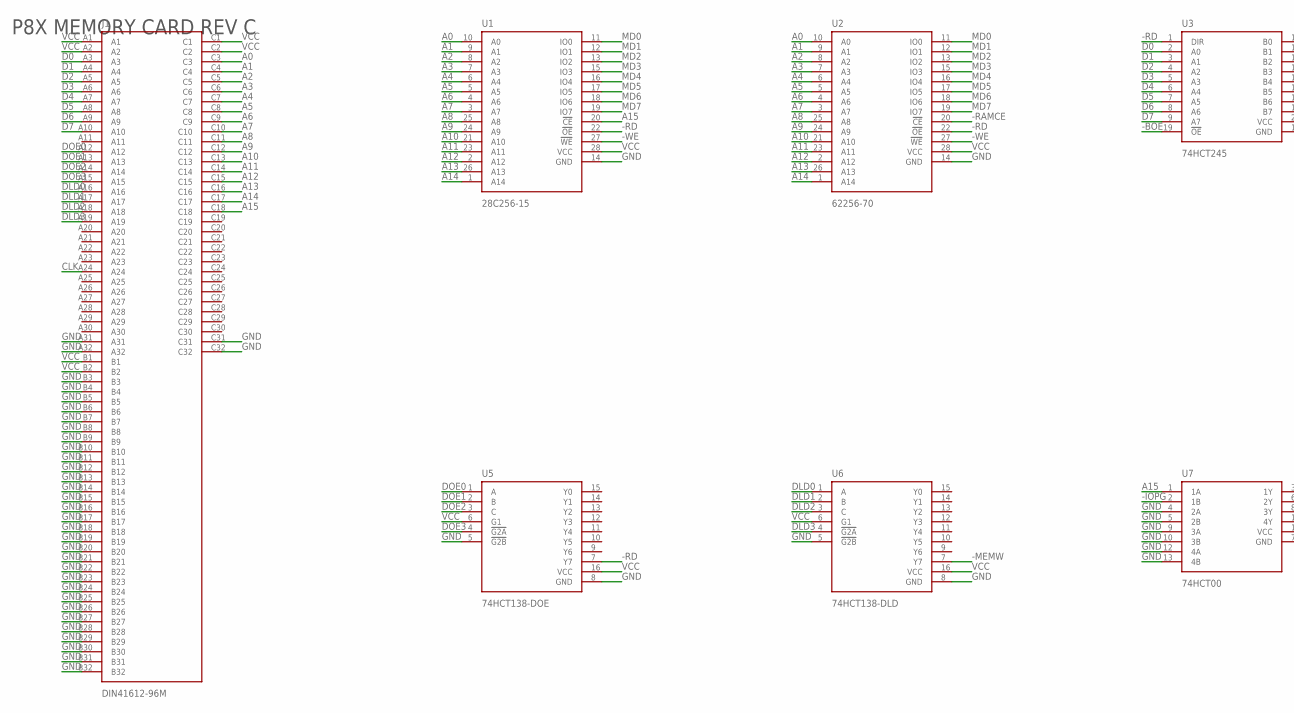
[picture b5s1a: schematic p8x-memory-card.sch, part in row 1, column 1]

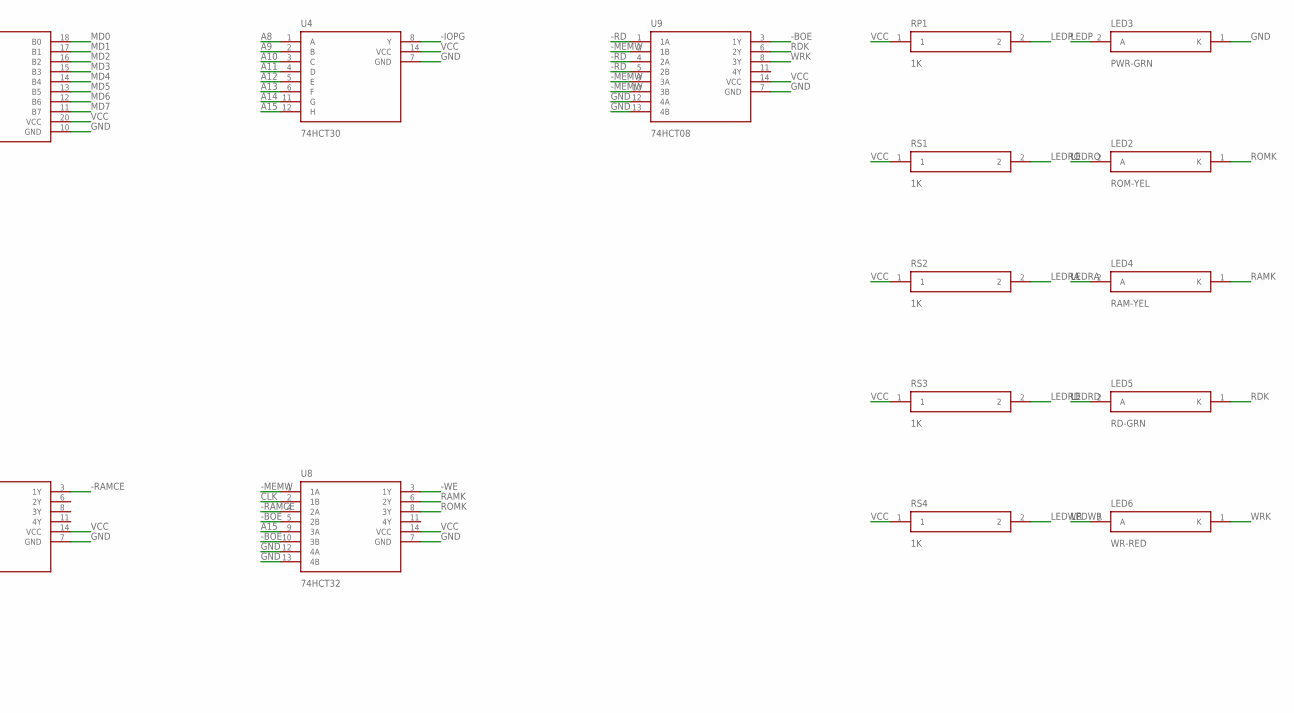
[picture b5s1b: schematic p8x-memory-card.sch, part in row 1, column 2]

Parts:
J1: DIN41612-96M; DIN96
LED2: ROM-YEL; LED5
LED3: PWR-GRN; LED5
LED4: RAM-YEL; LED5
LED5: RD-GRN; LED5
LED6: WR-RED; LED5
RP1: 1K; R_AXIAL
RS1, RS2, RS3, RS4: 1K; R_AXIAL
U1: 28C256-15; DIP28W
U2: 62256-70; DIP28W
U3: 74HCT245; DIP20
U4: 74HCT30; DIP14
U5: 74HCT138-DOE; DIP16
U6: 74HCT138-DLD; DIP16
U7: 74HCT00; DIP14
U8: 74HCT32; DIP14
U9: 74HCT08; DIP14

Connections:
-BOE: U3.19 (!OE), U8.5 (2B), U8.10 (3B), U9.3 (1Y)
-IOPG: U4.8 (Y), U7.2 (1B)
-MEMW: U6.7 (Y7), U8.1 (1A), U9.2 (1B), U9.9 (3A), U9.10 (3B)
-RAMCE: U2.20 (!CE), U7.3 (1Y), U8.4 (2A)
-RD: U1.22 (!OE), U2.22 (!OE), U3.1 (DIR), U5.7 (Y7), U9.1 (1A), U9.4 (2A), U9.5 (2B)
-WE: U1.27 (!WE), U2.27 (!WE), U8.3 (1Y)
A0: J1.C3, U1.10 (A0), U2.10 (A0)
A1: J1.C4, U1.9 (A1), U2.9 (A1)
A2: J1.C5, U1.8 (A2), U2.8 (A2)
A3: J1.C6, U1.7 (A3), U2.7 (A3)
A4: J1.C7, U1.6 (A4), U2.6 (A4)
A5: J1.C8, U1.5 (A5), U2.5 (A5)
A6: J1.C9, U1.4 (A6), U2.4 (A6)
A7: J1.C10, U1.3 (A7), U2.3 (A7)
A8: J1.C11, U1.25 (A8), U2.25 (A8), U4.1 (A)
A9: J1.C12, U1.24 (A9), U2.24 (A9), U4.2 (B)
A10: J1.C13, U1.21 (A10), U2.21 (A10), U4.3 (C)
A11: J1.C14, U1.23 (A11), U2.23 (A11), U4.4 (D)
A12: J1.C15, U1.2 (A12), U2.2 (A12), U4.5 (E)
A13: J1.C16, U1.26 (A13), U2.26 (A13), U4.6 (F)
A14: J1.C17, U1.1 (A14), U2.1 (A14), U4.11 (G)
A15: J1.C18, U1.20 (!CE), U4.12 (H), U7.1 (1A), U8.9 (3A)
CLK: J1.A24, U8.2 (1B)
D0: J1.A3, U3.2 (A0)
D1: J1.A4, U3.3 (A1)
D2: J1.A5, U3.4 (A2)
D3: J1.A6, U3.5 (A3)
D4: J1.A7, U3.6 (A4)
D5: J1.A8, U3.7 (A5)
D6: J1.A9, U3.8 (A6)
D7: J1.A10, U3.9 (A7)
DLD0: J1.A16, U6.1 (A)
DLD1: J1.A17, U6.2 (B)
DLD2: J1.A18, U6.3 (C)
DLD3: J1.A19, U6.4 (!G2A)
DOE0: J1.A12, U5.1 (A)
DOE1: J1.A13, U5.2 (B)
DOE2: J1.A14, U5.3 (C)
DOE3: J1.A15, U5.4 (!G2A)
GND: J1.A31, J1.A32, J1.B3, J1.B4, J1.B5, J1.B6, J1.B7, J1.B8, J1.B9, J1.B10, J1.B11, J1.B12, J1.B13, J1.B14, J1.B15, J1.B16, J1.B17, J1.B18, J1.B19, J1.B20, J1.B21, J1.B22, J1.B23, J1.B24, J1.B25, J1.B26, J1.B27, J1.B28, J1.B29, J1.B30, J1.B31, J1.B32, J1.C31, J1.C32, LED3.1 (K), U1.14 (GND), U2.14 (GND), U3.10 (GND), U4.7 (GND), U5.5 (!G2B), U5.8 (GND), U6.5 (!G2B), U6.8 (GND), U7.4 (2A), U7.5 (2B), U7.7 (GND), U7.9 (3A), U7.10 (3B), U7.12 (4A), U7.13 (4B), U8.7 (GND), U8.12 (4A), U8.13 (4B), U9.7 (GND), U9.12 (4A), U9.13 (4B)
LEDP: LED3.2 (A), RP1.2
LEDRA: LED4.2 (A), RS2.2
LEDRD: LED5.2 (A), RS3.2
LEDRO: LED2.2 (A), RS1.2
LEDWR: LED6.2 (A), RS4.2
MD0: U1.11 (IO0), U2.11 (IO0), U3.18 (B0)
MD1: U1.12 (IO1), U2.12 (IO1), U3.17 (B1)
MD2: U1.13 (IO2), U2.13 (IO2), U3.16 (B2)
MD3: U1.15 (IO3), U2.15 (IO3), U3.15 (B3)
MD4: U1.16 (IO4), U2.16 (IO4), U3.14 (B4)
MD5: U1.17 (IO5), U2.17 (IO5), U3.13 (B5)
MD6: U1.18 (IO6), U2.18 (IO6), U3.12 (B6)
MD7: U1.19 (IO7), U2.19 (IO7), U3.11 (B7)
RAMK: LED4.1 (K), U8.6 (2Y)
RDK: LED5.1 (K), U9.6 (2Y)
ROMK: LED2.1 (K), U8.8 (3Y)
VCC: J1.A1, J1.A2, J1.B1, J1.B2, J1.C1, J1.C2, RP1.1, RS1.1, RS2.1, RS3.1, RS4.1, U1.28 (VCC), U2.28 (VCC), U3.20 (VCC), U4.14 (VCC), U5.6 (G1), U5.16 (VCC), U6.6 (G1), U6.16 (VCC), U7.14 (VCC), U8.14 (VCC), U9.14 (VCC)
WRK: LED6.1 (K), U9.8 (3Y)

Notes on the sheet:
P8X MEMORY CARD REV C

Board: 4 copper layers, 20 parts (0 on the bottom side), 58 nets, no tracks yet.
